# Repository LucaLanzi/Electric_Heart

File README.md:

# Electric_Heart
An attempt to make a lovers box, a gift for my special someone which shows telemetry, displays messages I send, and that serves as a variety of multimedia goodies. Based on an ESP32 Nano, and a whole heap of COTS parts.
Currently  a work in progress.

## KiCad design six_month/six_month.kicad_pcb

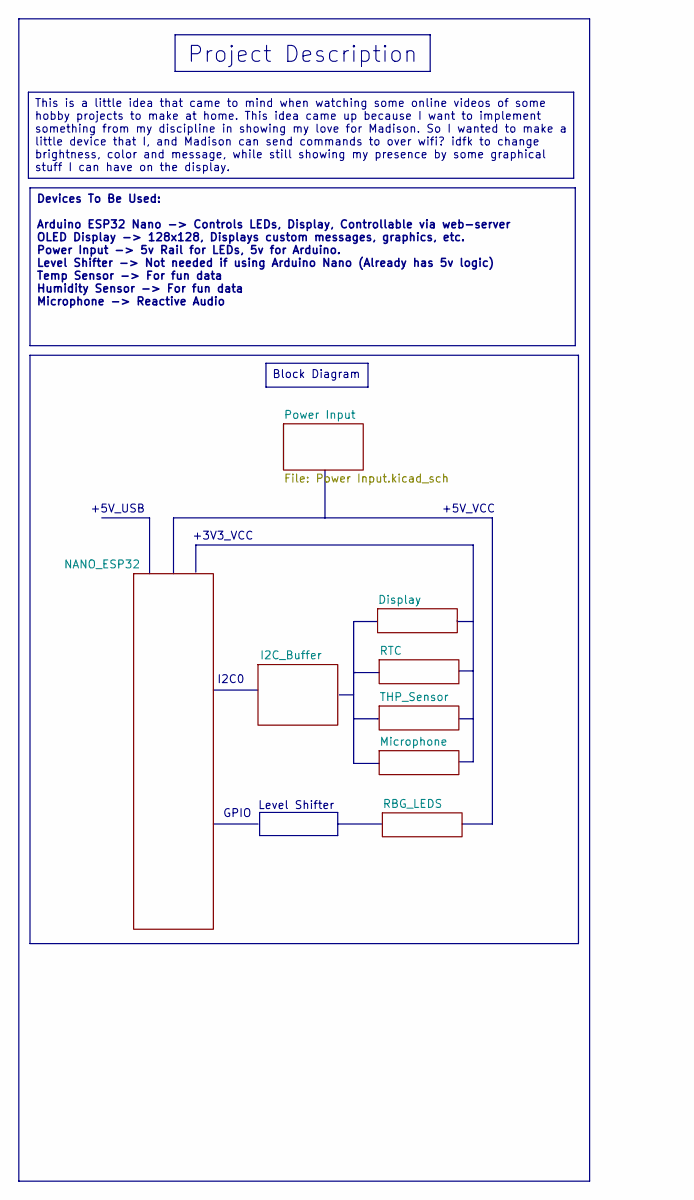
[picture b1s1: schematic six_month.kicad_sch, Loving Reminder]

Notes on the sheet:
GPIO
+3V3_VCC
+5V_VCC
+5V_USB
Project Description
I2C0
Level Shifter
Devices To Be Used: Arduino ESP32 Nano -> Controls LEDs, Display, Controllable via web-server OLED Display -> 128x128, Displays custom messages, graphics, etc. Power Input -> 5v Rail for LEDs, 5v for Arduino. Level Shifter -> Not needed if using Arduino Nano (Already has 5v logic) Temp Sensor -> Fo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
Block Diagram
This is a little idea that came to mind when watching some online videos of some hobby projects to make at home. This idea came up because I want to implement something from my discipline in showing my love for Madison. So I wanted to make a little device that I, and Madison can send commands to ov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

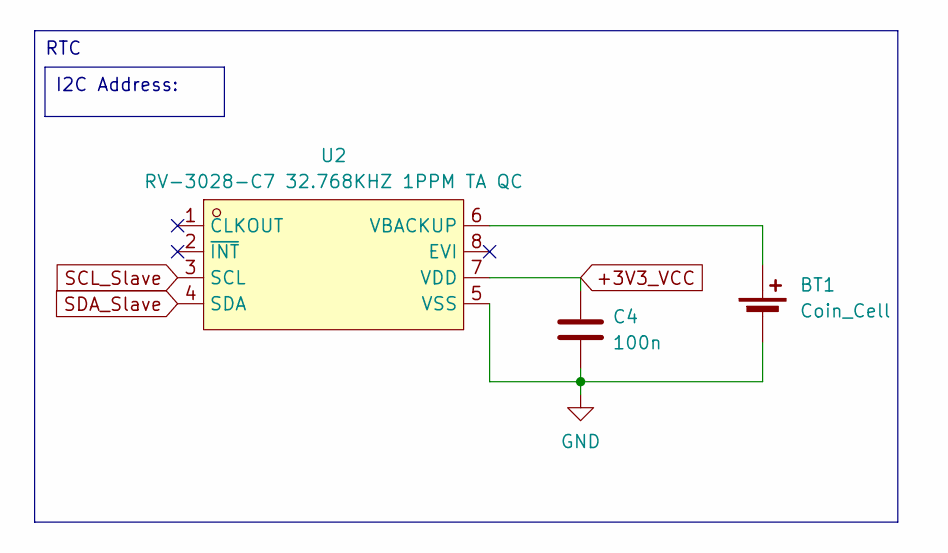
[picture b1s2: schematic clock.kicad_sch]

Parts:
BT1: Coin_Cell; Battery_Panasonic_CR2032-HFN_Horizontal_CircularHoles
C4: 100n; C_0402_1005Metric
U2: RV-3028-C7 32.768KHZ 1PPM TA QC; OSC-SMD_8P-L3.2-W1.5-P0.90-BL; LCSC Part C3019759

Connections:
+3V3_VCC: C4.1, U2.7 (VDD); also elsewhere on the board
GND: BT1.2 (-), C4.2, U2.5 (VSS); also elsewhere on the board
unnamed: BT1.1 (+), U2.6 (VBACKUP)
SCL_Slave: U2.3 (SCL); also elsewhere on the board
SDA_Slave: U2.4 (SDA); also elsewhere on the board

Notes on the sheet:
I2C Address:
RTC

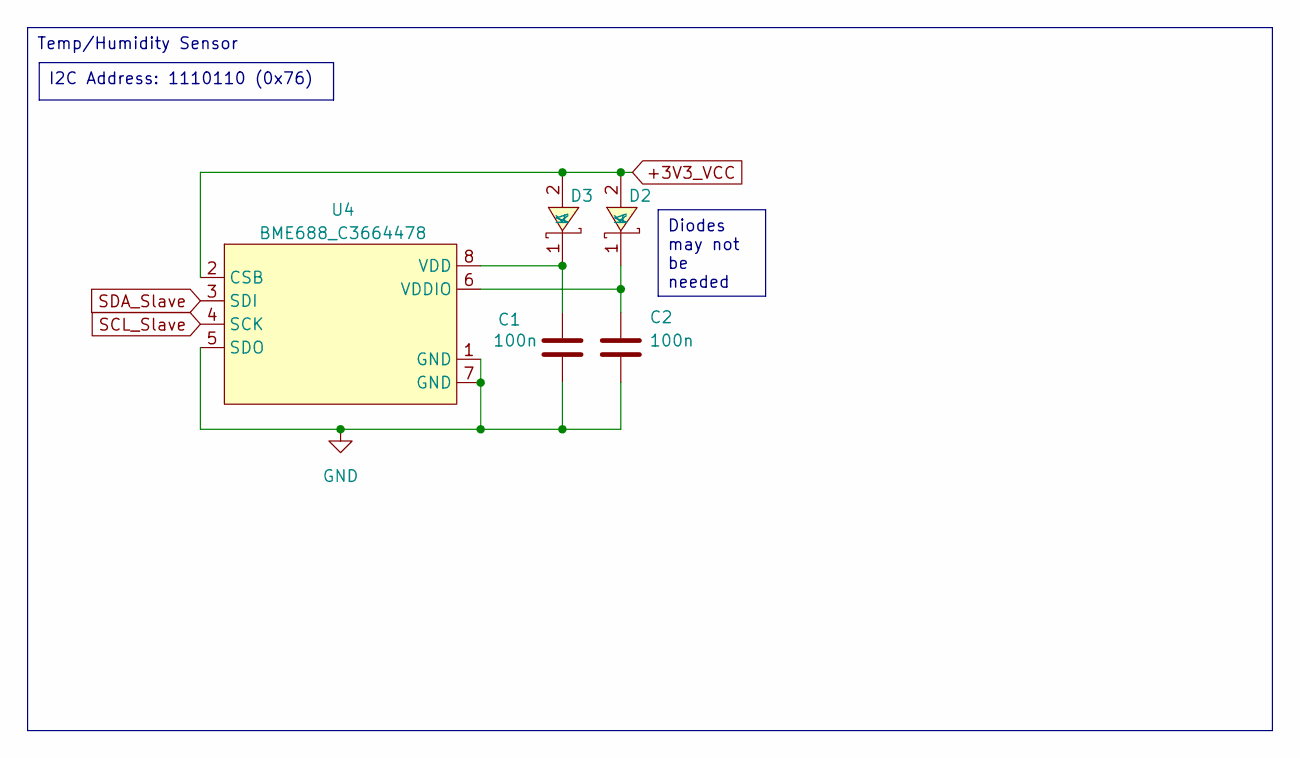
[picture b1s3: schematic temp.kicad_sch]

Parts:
C1, C2: 100n; C_0402_1005Metric
D2, D3: B340A-13-F; SMA_L4.4-W2.6-LS5.0-RD; LCSC Part C85098
U4: BME688_C3664478; LGA-8_L3.0-W3.0-P0.80_BME688; LCSC Part C3664478

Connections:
+3V3_VCC: D2.2 (A), D3.2 (A), U4.2 (CSB); also elsewhere on the board
GND: C1.2, C2.2, U4.1 (GND), U4.5 (SDO), U4.7 (GND); also elsewhere on the board
unnamed: C2.1, D2.1 (K), U4.6 (VDDIO)
unnamed: C1.1, D3.1 (K), U4.8 (VDD)
SCL_Slave: U4.4 (SCK); also elsewhere on the board
SDA_Slave: U4.3 (SDI); also elsewhere on the board

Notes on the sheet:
Diodes may not be needed
I2C Address: 1110110 (0x76)
Temp/Humidity Sensor

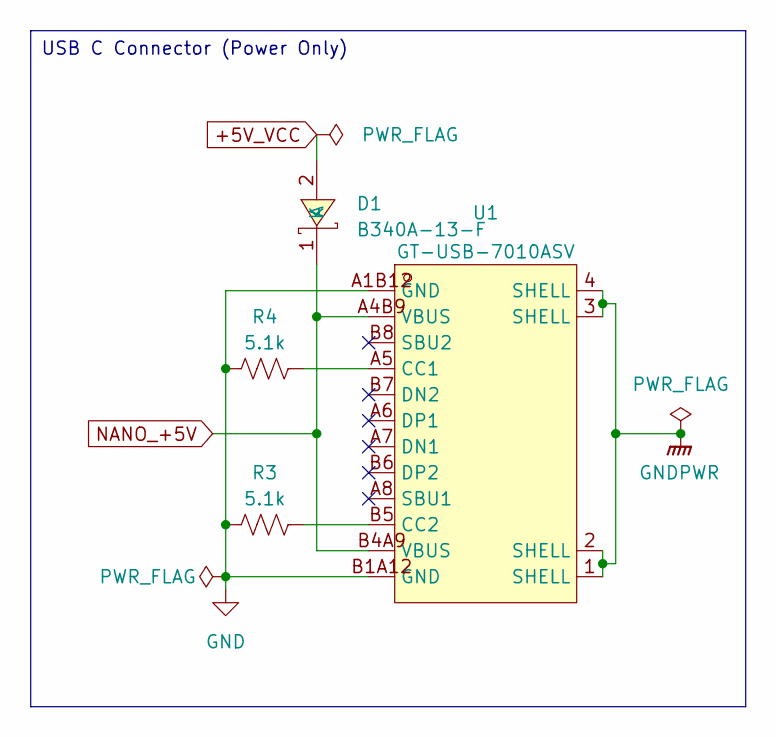
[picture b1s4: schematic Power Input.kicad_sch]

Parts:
D1: B340A-13-F; SMA_L4.4-W2.6-LS5.0-RD; LCSC Part C85098
R3, R4: 5.1k; R_0402_1005Metric
U1: GT-USB-7010ASV; USB-C-SMD_G-SWITCH_GT-USB-7010ASV; LCSC Part C2988369

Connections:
+5V_VCC: D1.2 (A); also elsewhere on the board
GND: R3.2, R4.2, U1.A1B12 (GND), U1.B1A12 (GND); also elsewhere on the board
GNDPWR: U1.1 (SHELL), U1.2 (SHELL), U1.3 (SHELL), U1.4 (SHELL)
NANO_+5V: D1.1 (K), U1.A4B9 (VBUS), U1.B4A9 (VBUS); also elsewhere on the board
unnamed: R4.1, U1.A5 (CC1)
unnamed: R3.1, U1.B5 (CC2)

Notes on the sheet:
USB C Connector (Power Only)

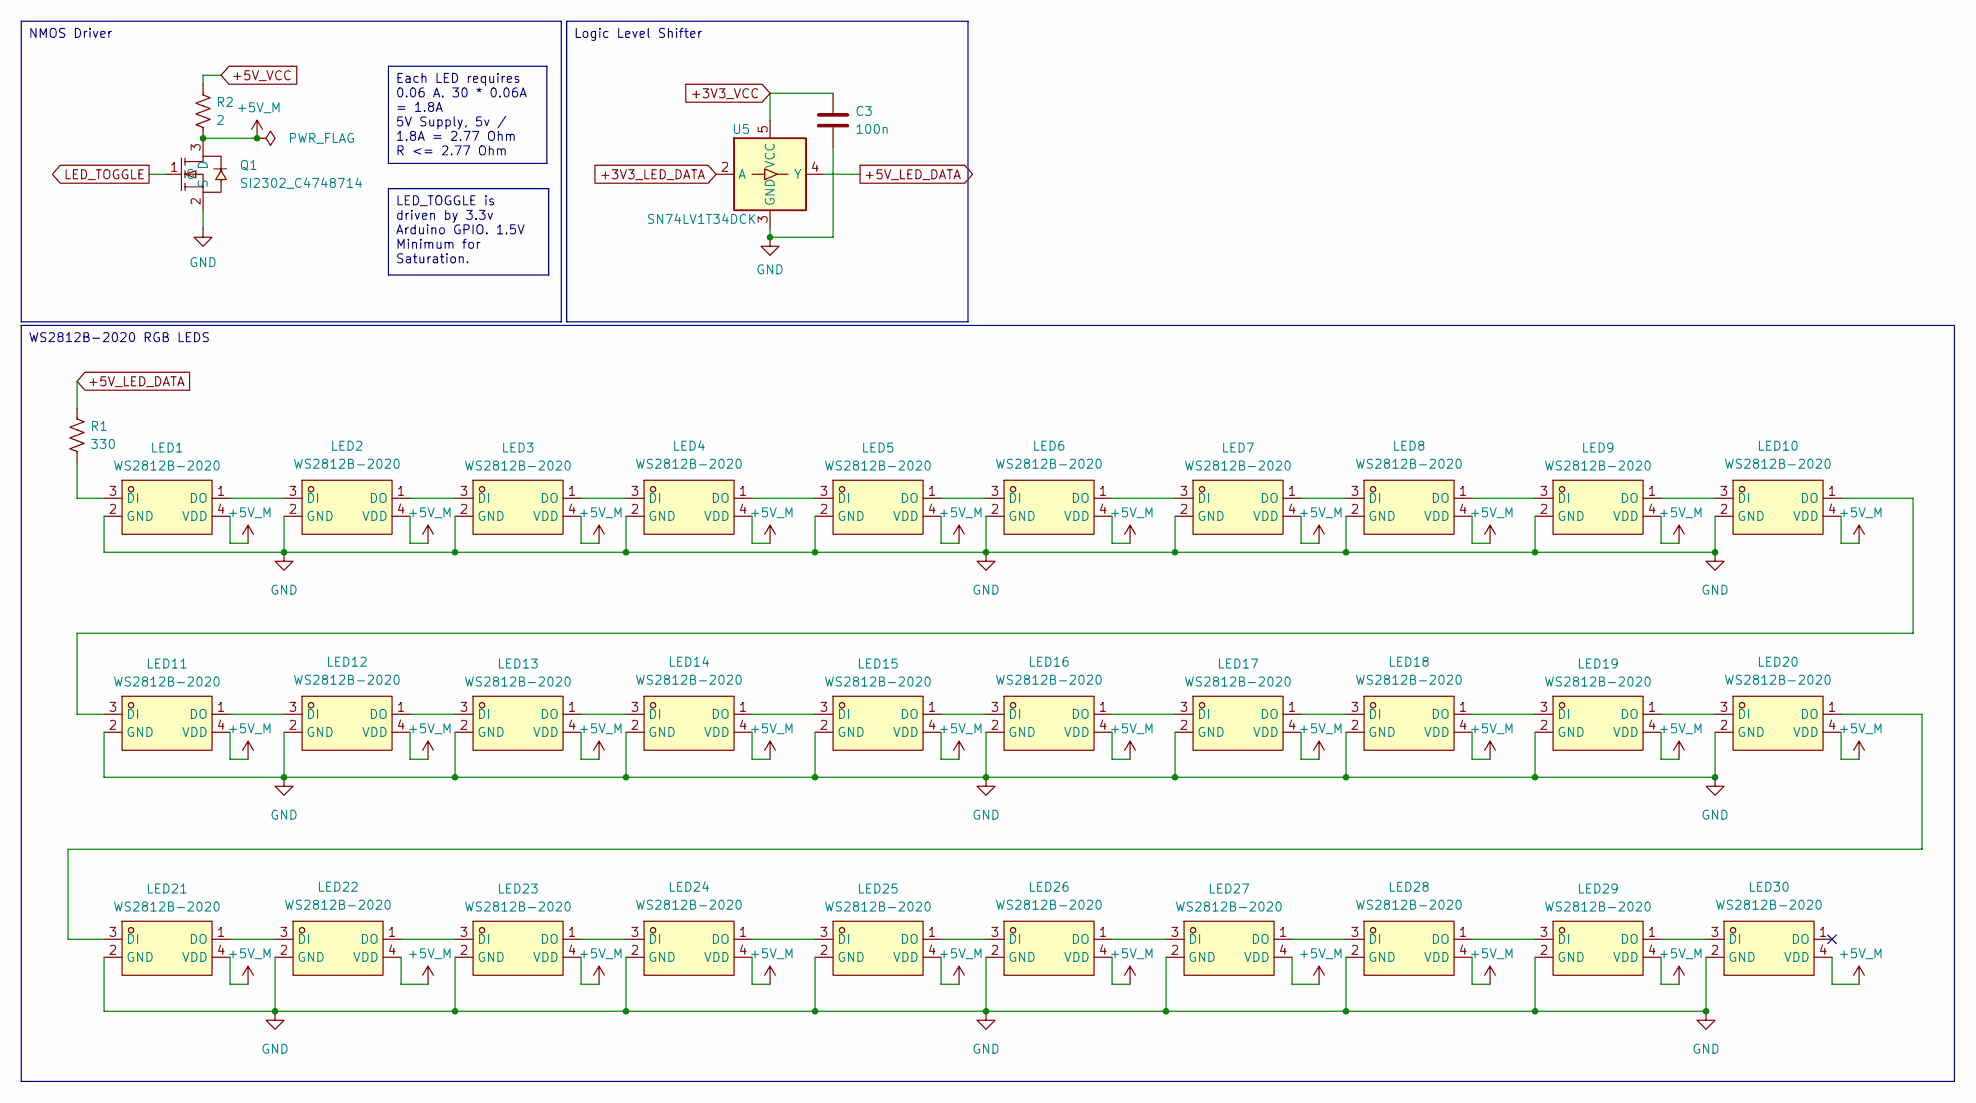
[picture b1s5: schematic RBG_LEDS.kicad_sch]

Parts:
C3: 100n; C_0402_1005Metric
LED1, LED2, LED3, LED4, LED5, LED6, LED7, LED8, LED9, LED10, LED11, LED12, LED13, LED14, LED15, LED16, LED17, LED18, LED19, LED20, LED21, LED22, LED23, LED24, LED25, LED26, LED27, LED28, LED29, LED30: WS2812B-2020; LED-SMD_4P-L2.0-W2.0-TL_WS2812B-2020; LCSC Part C965555
Q1: SI2302_C4748714; SOT-23-3_L2.9-W1.3-P1.90-LS2.4-BR; LCSC Part C4748714
R1: 330; R_0402_1005Metric
R2: 2; R_0402_1005Metric
U5: SN74LV1T34DCK; SOT-353_SC-70-5

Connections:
+3V3_LED_DATA: U5.2 (A); also elsewhere on the board
+3V3_VCC: C3.1, U5.5 (VCC); also elsewhere on the board
+5V_LED_DATA: R1.1, U5.4 (Y)
+5V_M: LED1.4 (VDD), LED2.4 (VDD), LED3.4 (VDD), LED4.4 (VDD), LED5.4 (VDD), LED6.4 (VDD), LED7.4 (VDD), LED8.4 (VDD), LED9.4 (VDD), LED10.4 (VDD), LED11.4 (VDD), LED12.4 (VDD), LED13.4 (VDD), LED14.4 (VDD), LED15.4 (VDD), LED16.4 (VDD), LED17.4 (VDD), LED18.4 (VDD), LED19.4 (VDD), LED20.4 (VDD), LED21.4 (VDD), LED22.4 (VDD), LED23.4 (VDD), LED24.4 (VDD), LED25.4 (VDD), LED26.4 (VDD), LED27.4 (VDD), LED28.4 (VDD), LED29.4 (VDD), LED30.4 (VDD), Q1.3 (D), R2.2
+5V_VCC: R2.1; also elsewhere on the board
GND: C3.2, LED1.2 (GND), LED2.2 (GND), LED3.2 (GND), LED4.2 (GND), LED5.2 (GND), LED6.2 (GND), LED7.2 (GND), LED8.2 (GND), LED9.2 (GND), LED10.2 (GND), LED11.2 (GND), LED12.2 (GND), LED13.2 (GND), LED14.2 (GND), LED15.2 (GND), LED16.2 (GND), LED17.2 (GND), LED18.2 (GND), LED19.2 (GND), LED20.2 (GND), LED21.2 (GND), LED22.2 (GND), LED23.2 (GND), LED24.2 (GND), LED25.2 (GND), LED26.2 (GND), LED27.2 (GND), LED28.2 (GND), LED29.2 (GND), LED30.2 (GND), Q1.2 (S), U5.3 (GND); also elsewhere on the board
LED_TOGGLE: Q1.1 (G); also elsewhere on the board
unnamed: LED1.3 (DI), R1.2
unnamed: LED1.1 (DO), LED2.3 (DI)
unnamed: LED2.1 (DO), LED3.3 (DI)
unnamed: LED3.1 (DO), LED4.3 (DI)
unnamed: LED4.1 (DO), LED5.3 (DI)
unnamed: LED5.1 (DO), LED6.3 (DI)
unnamed: LED6.1 (DO), LED7.3 (DI)
unnamed: LED7.1 (DO), LED8.3 (DI)
unnamed: LED8.1 (DO), LED9.3 (DI)
unnamed: LED9.1 (DO), LED10.3 (DI)
unnamed: LED10.1 (DO), LED11.3 (DI)
unnamed: LED11.1 (DO), LED12.3 (DI)
unnamed: LED12.1 (DO), LED13.3 (DI)
unnamed: LED13.1 (DO), LED14.3 (DI)
unnamed: LED14.1 (DO), LED15.3 (DI)
unnamed: LED15.1 (DO), LED16.3 (DI)
unnamed: LED16.1 (DO), LED17.3 (DI)
unnamed: LED17.1 (DO), LED18.3 (DI)
unnamed: LED18.1 (DO), LED19.3 (DI)
unnamed: LED19.1 (DO), LED20.3 (DI)
unnamed: LED20.1 (DO), LED21.3 (DI)
unnamed: LED21.1 (DO), LED22.3 (DI)
unnamed: LED22.1 (DO), LED23.3 (DI)
unnamed: LED23.1 (DO), LED24.3 (DI)
unnamed: LED24.1 (DO), LED25.3 (DI)
unnamed: LED25.1 (DO), LED26.3 (DI)
unnamed: LED26.1 (DO), LED27.3 (DI)
unnamed: LED27.1 (DO), LED28.3 (DI)
unnamed: LED28.1 (DO), LED29.3 (DI)
unnamed: LED29.1 (DO), LED30.3 (DI)

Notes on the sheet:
NMOS Driver
Each LED requires 0.06 A. 30 * 0.06A = 1.8A 5V Supply, 5v / 1.8A = 2.77 Ohm R <= 2.77 Ohm
LED_TOGGLE is driven by 3.3v Arduino GPIO. 1.5V Minimum for Saturation.
WS2812B-2020 RGB LEDS
Logic Level Shifter

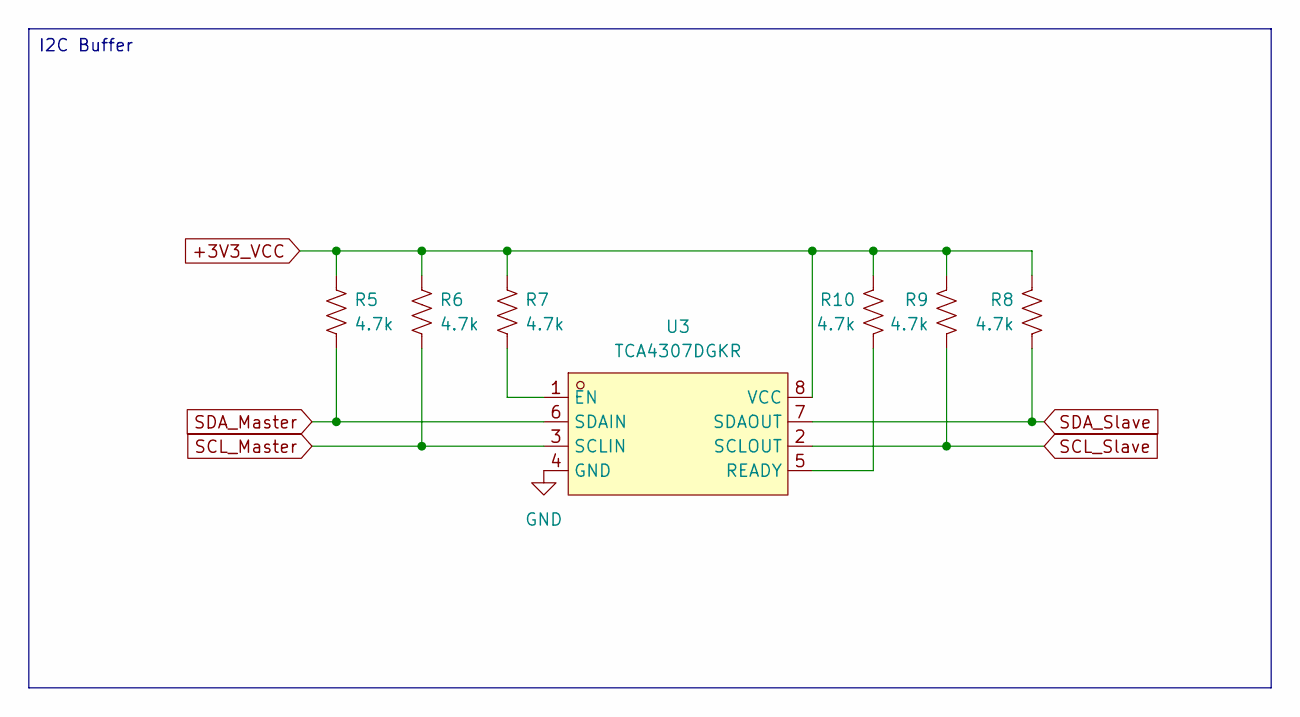
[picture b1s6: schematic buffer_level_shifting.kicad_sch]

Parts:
R5, R6, R7, R8, R9, R10: 4.7k; R_0402_1005Metric
U3: TCA4307DGKR; VSSOP-8_L3.0-W3.0-P0.65-LS4.9-BL; LCSC Part C880333

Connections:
+3V3_VCC: R5.1, R6.1, R7.1, R8.1, R9.1, R10.1, U3.8 (VCC); also elsewhere on the board
GND: U3.4 (GND); also elsewhere on the board
unnamed: R7.2, U3.1 (EN)
unnamed: R10.2, U3.5 (READY)
SCL_Master: R6.2, U3.3 (SCLIN); also elsewhere on the board
SCL_Slave: R9.2, U3.2 (SCLOUT); also elsewhere on the board
SDA_Master: R5.2, U3.6 (SDAIN); also elsewhere on the board
SDA_Slave: R8.2, U3.7 (SDAOUT); also elsewhere on the board

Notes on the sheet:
I2C Buffer

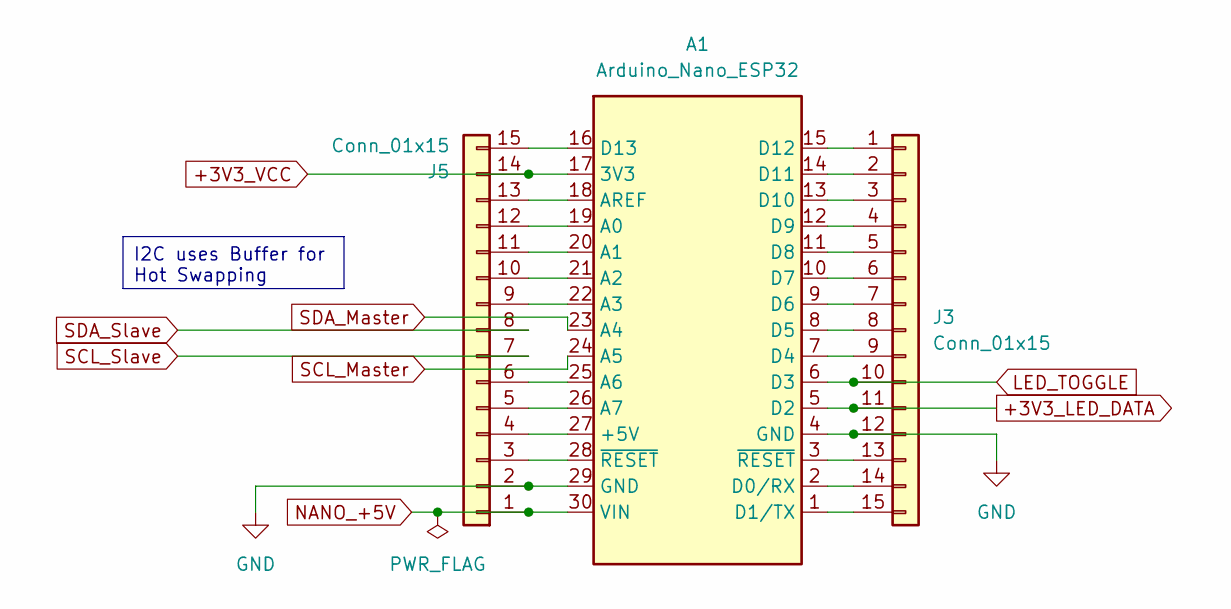
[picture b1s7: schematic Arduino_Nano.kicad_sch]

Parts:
A1: Arduino_Nano_ESP32; Arduino_Nano
J3, J5: Conn_01x15; PinHeader_1x15_P2.54mm_Vertical

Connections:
+3V3_LED_DATA: A1.5 (D2), J3.11; also elsewhere on the board
+3V3_VCC: A1.17 (3V3), J5.14; also elsewhere on the board
GND: A1.4 (GND), A1.29 (GND), J3.12, J5.2; also elsewhere on the board
LED_TOGGLE: A1.6 (D3), J3.10; also elsewhere on the board
NANO_+5V: A1.30 (VIN), J5.1; also elsewhere on the board
unnamed: A1.27 (+5V), J5.4
unnamed: A1.19 (A0), J5.12
unnamed: A1.20 (A1), J5.11
unnamed: A1.21 (A2), J5.10
unnamed: A1.22 (A3), J5.9
unnamed: A1.25 (A6), J5.6
unnamed: A1.26 (A7), J5.5
unnamed: A1.18 (AREF), J5.13
unnamed: A1.2 (D0/RX), J3.14
unnamed: A1.1 (D1/TX), J3.15
unnamed: A1.7 (D4), J3.9
unnamed: A1.8 (D5), J3.8
unnamed: A1.9 (D6), J3.7
unnamed: A1.10 (D7), J3.6
unnamed: A1.11 (D8), J3.5
unnamed: A1.12 (D9), J3.4
unnamed: A1.13 (D10), J3.3
unnamed: A1.14 (D11), J3.2
unnamed: A1.15 (D12), J3.1
unnamed: A1.16 (D13), J5.15
unnamed: A1.3 (~RESET), J3.13
unnamed: A1.28 (~RESET), J5.3
SCL_Master: A1.24 (A5); also elsewhere on the board
SCL_Slave: J5.7; also elsewhere on the board
SDA_Master: A1.23 (A4); also elsewhere on the board
SDA_Slave: J5.8; also elsewhere on the board

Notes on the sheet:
I2C uses Buffer for Hot Swapping

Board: 4 copper layers, 57 parts (0 on the bottom side), 72 nets, no tracks yet.

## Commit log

2025-08-06 README.md
2025-08-06 WIP Commit
    Migrated from local workspace.
2025-08-06 WIP: Updated Software Design Block
    Starting brainstorming the software integration. Starting High level conceptual, then moving more low level and subprocesses come to mind.
2025-08-06 Changes
    Removed the microphone idea, added a DAC for Bluetooth to Line out. Allows for external speakers to be connected via an Aux cable
2025-08-06 Added Audio Connector
    Included 3.5mm TRS for External Speakers from the DAC.
2025-08-20 Removed some stuff
    Removed the speaker stuff because we dont need it.
